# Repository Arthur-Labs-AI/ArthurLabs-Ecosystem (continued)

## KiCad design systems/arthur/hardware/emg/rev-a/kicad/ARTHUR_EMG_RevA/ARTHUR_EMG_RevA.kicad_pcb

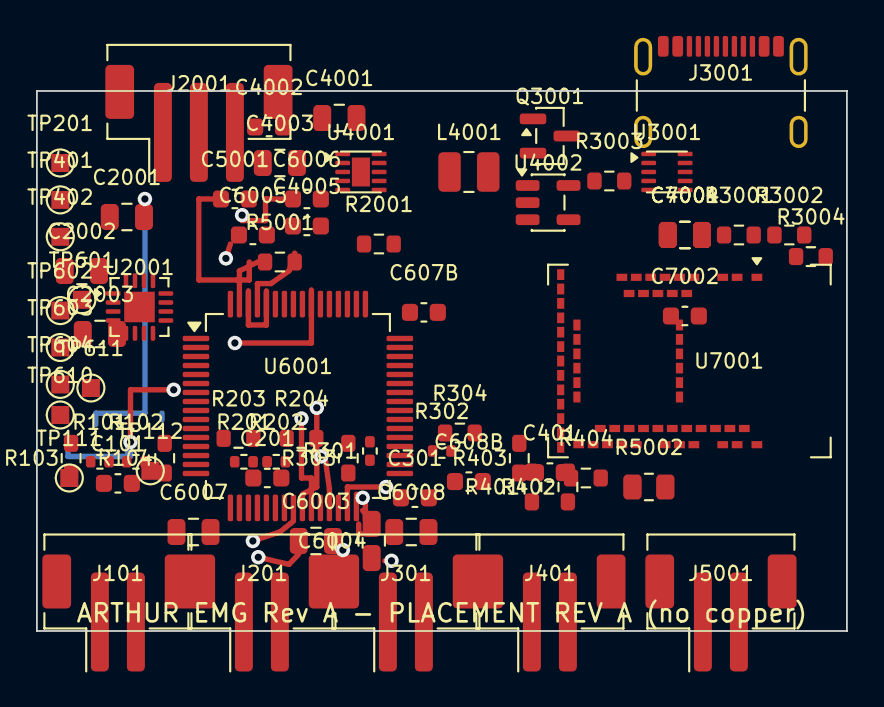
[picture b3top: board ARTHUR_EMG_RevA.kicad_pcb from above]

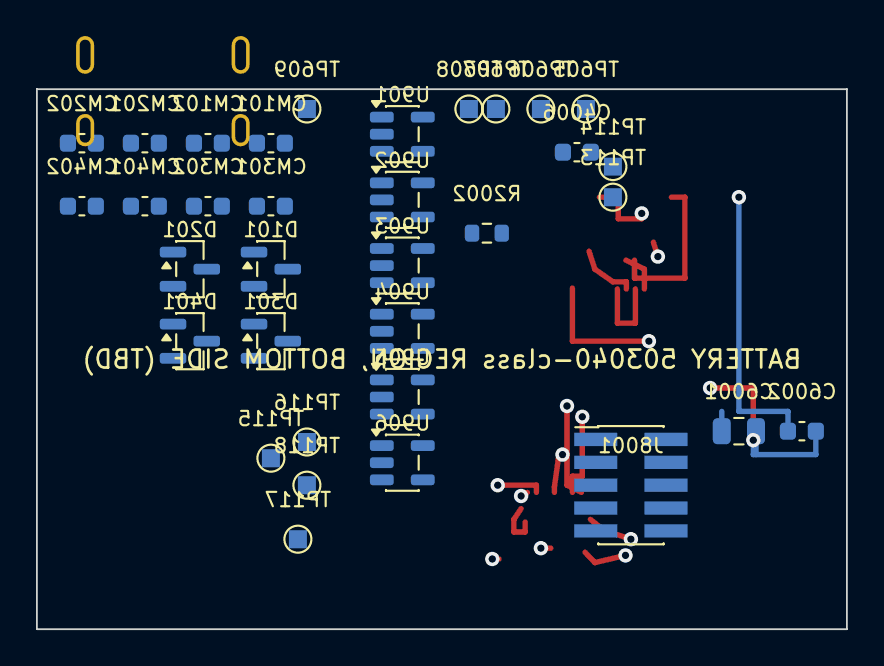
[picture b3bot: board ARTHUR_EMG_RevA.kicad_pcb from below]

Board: 4 copper layers, 45.0 x 30.0 mm, 106 parts (34 on the bottom side), 54 nets.

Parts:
C101, C201, C301, C401: 4.7nF C0G; C_0603_1608Metric
C607B, C608B, C4002, C6002, C7002: 0.1u; C_0603_1608Metric
C2001: 1u; C_0805_2012Metric
C2002, C2003, C7001: 4.7u; C_0805_2012Metric
C4001, C4003, C4004, C6001: 10u; C_0805_2012Metric
C4005, C4006, C6004, C6005, C6006, C6007, C6008: 1u; C_0603_1608Metric
C5001: 1.5nF; C_0603_1608Metric
C6003: 22u; C_0805_2012Metric
CM101, CM102, CM201, CM202, CM301, CM302, CM401, CM402: 470p DNP; C_0603_1608Metric
D101, D201, D301, D401: TVS DNP; SOT-23
J101: EMG-CH1; JST_PH_B2B-PH-SM4-TB_1x02-1MP_P2.00mm_Vertical
J201: EMG-CH2; JST_PH_B2B-PH-SM4-TB_1x02-1MP_P2.00mm_Vertical
J301: EMG-CH3; JST_PH_B2B-PH-SM4-TB_1x02-1MP_P2.00mm_Vertical
J401: EMG-CH4; JST_PH_B2B-PH-SM4-TB_1x02-1MP_P2.00mm_Vertical
J2001: LiPo-3P; JST_PH_B3B-PH-SM4-TB_1x03-1MP_P2.00mm_Vertical
J3001: USB-C-16P; USB_C_Receptacle_GCT_USB4105-xx-A_16P_TopMnt_Horizontal
J5001: RLD; JST_PH_B2B-PH-SM4-TB_1x02-1MP_P2.00mm_Vertical
J8001: SWD-10; PinHeader_2x05_P1.27mm_Vertical_SMD
L4001: 1.5uH; L_1008_2520Metric
Q3001: 2N7002; SOT-23
R101, R102, R201, R202, R301, R302: 2.2k 1%; R_0402_1005Metric
R103, R104, R203, R204, R303, R304, R403, R404: 390k 1%; R_0603_1608Metric
R401, R402: 2.2k 1%; R_0603_1608Metric
R2001: 3.57k; R_0603_1608Metric
R2002: 3.24k; R_0603_1608Metric
R3001, R3002: 5.1k; R_0603_1608Metric
R3003, R3004: 100k; R_0603_1608Metric
R5001: 1M; R_0603_1608Metric
R5002: 100k; R_0805_2012Metric
TP111, TP112, TP113, TP114, TP115, TP116, TP117, TP118, TP201, TP401, TP402, TP601, TP602, TP603, TP604, TP605, TP606, TP607, TP608, TP609, TP610, TP611: TP_SMD; TP_SMD_1x1mm
U901, U902, U903, U904, U905, U906: SN74LVC1G125; SOT-23-5
U2001: BQ24074RGTR; QFN-16-1EP_3x3mm_P0.5mm_EP1.7x1.7mm
U3001: TPD4E05U06DQAR; TPD4E05U06_DQA_2x2mm_P0.5mm
U4001: TPS63031DSKR; TPS63031_DSK_2.5x2.0mm_P0.5mm
U4002: TPS7A2030PDBVR; SOT-23-5
U6001: ADS1294IPAG; TQFP-64_10x10mm_P0.5mm
U7001: MDBT50Q-1MV2; Raytac_MDBT50Q

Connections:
3V3: C608B.1, C4003.1, C4004.1, C4005.1, C6008.1, C7001.1, C7002.1, J8001.1, R3003.1, TP401.1, U4001.1, U4001.10, U4002.1, U6001.48, U6001.50, U6001.52, U7001.28, U7001.30
AFE_3V0: C607B.1, C4006.1, C6007.1, TP601.1, U901.5, U902.5, U903.5, U904.5, U905.5, U906.5, U4002.5, U6001.1, U6001.2, U6001.3, U6001.4, U6001.5, U6001.6, U6001.7, U6001.8, U6001.19, U6001.21, U6001.22, U6001.54, U6001.56, U6001.59
AFE_CS_N: TP607.1, U903.4, U6001.39
AFE_DRDY_N: TP608.1, U6001.47, U7001.41
AFE_ENABLE: Q3001.3, R3003.2, U4002.3
AFE_MISO: TP606.1, U6001.43, U7001.39
AFE_MOSI: TP605.1, U902.4, U6001.34
AFE_PWDN_N: TP611.1, U906.4, U6001.35
AFE_RESET_N: TP610.1, U905.4, U6001.36
AFE_SCLK: TP604.1, U901.4, U6001.40
AFE_START: TP609.1, U904.4, U6001.38
BAT+: C2003.1, J2001.1, TP201.1, U2001.2, U2001.3
CC1: J3001.A5, R3001.1, U3001.4
CC2: J3001.B5, R3002.1, U3001.5
CH1_N: C101.2, CM102.1, D101.3, R102.2, R104.1, TP112.1, U6001.15
CH1_P: C101.1, CM101.1, D101.1, R101.2, R103.1, TP111.1, U6001.16
CH2_N: C201.2, CM202.1, D201.3, R202.2, R204.1, TP114.1, U6001.13
CH2_P: C201.1, CM201.1, D201.1, R201.2, R203.1, TP113.1, U6001.14
CH3_N: C301.2, CM302.1, D301.3, R302.2, R304.1, TP116.1, U6001.11
CH3_P: C301.1, CM301.1, D301.1, R301.2, R303.1, TP115.1, U6001.12
CH4_N: C401.2, CM402.1, D401.3, R402.2, R404.1, TP118.1, U6001.9
CH4_P: C401.1, CM401.1, D401.1, R401.2, R403.1, TP117.1, U6001.10
CHG_N: U2001.9, U7001.45
ELECTRODE_N: J101.2, J201.2, J301.2, J401.2, R102.1, R202.1, R302.1, R402.1
ELECTRODE_P: J101.1, J201.1, J301.1, J401.1, R101.1, R201.1, R301.1, R401.1
GND: C607B.2, C608B.2, C2001.2, C2002.2, C2003.2, C4001.2, C4002.2, C4003.2, C4004.2, C4005.2, C4006.2, C6001.2, C6002.2, C6003.2, C6004.2, C6005.2, C6006.2, C6007.2, C6008.2, C7001.2, C7002.2, CM101.2, CM102.2, CM201.2, CM202.2, CM301.2, CM302.2, CM401.2, CM402.2, D101.2, D201.2, D301.2, D401.2, J101.MP, J201.MP, J301.MP, J401.MP, J2001.3, J2001.MP, J3001.A1, J3001.A12, J3001.B1, J3001.B12, J5001.2, J5001.MP, J8001.3, J8001.5, J8001.9, Q3001.2, R2001.2, R2002.2, R3001.2, R3002.2, R3004.2, TP402.1, U901.1, U901.3, U902.1, U902.3, U903.1, U903.3, U904.1, U904.3, U905.1, U905.3, U906.1, U906.3, U2001.4, U2001.5, U2001.8, U2001.17, U3001.3, U3001.8, U4001.3, U4001.7, U4001.9, U4001.11, U4002.2, U6001.20, U6001.23, U6001.25, U6001.31, U6001.32, U6001.33, U6001.41, U6001.49, U6001.51, U6001.53, U6001.57, U6001.58, U7001.1, U7001.2, U7001.15, U7001.33, U7001.55
ICHG_SET_TBD: R2001.1, U2001.16
ILIM_SET_TBD: R2002.1, U2001.12
MCU_CS_N: U903.2, U7001.38
MCU_MOSI: U902.2, U7001.36
MCU_PWDN_N: U906.2, U7001.43
MCU_RESET_N: J8001.10, U7001.40
MCU_RESET_N_AFE: U905.2, U7001.44
MCU_SCLK: U901.2, U7001.37
MCU_START: U904.2, U7001.42
PACK_NTC: J2001.2, U2001.1
PGOOD_N: U2001.7, U7001.48
RLDINV: C5001.2, R5001.2, U6001.61
RLDOUT: C5001.1, R5001.1, R5002.1, TP603.1, U6001.63
RLD_SAFE: J5001.1, R5002.2
SWDCLK: J8001.4, U7001.53
SWDIO: J8001.2, U7001.51
SW_L1: L4001.1, U4001.4
SW_L2: L4001.2, U4001.2
SYS_RAW: C2002.1, C4001.1, C4002.1, U2001.6, U2001.10, U2001.11, U4001.5, U4001.6, U4001.8
USB_D+: J3001.A6, J3001.B6, U3001.1, U7001.35
USB_D-: J3001.A7, J3001.B7, U3001.2, U7001.34
USB_VBUS: C2001.1, J3001.A4, J3001.A9, J3001.B4, J3001.B9, Q3001.1, R3004.1, U2001.13, U7001.32
VCAP1: C6003.1, U6001.28
VCAP2: C6004.1, U6001.30
VCAP3: C6005.1, U6001.55
VCAP4: C6006.1, U6001.26
VCM: R103.2, R104.2, R203.2, R204.2, R303.2, R304.2, R403.2, R404.2, TP602.1, U6001.60, U6001.62
VREFP_2V4: C6001.1, C6002.1, U6001.24

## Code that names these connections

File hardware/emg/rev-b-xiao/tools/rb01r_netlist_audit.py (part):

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# SCTF SX3M (3CM) family datasheet rev 05/12/2026, "Dimensions" page
DATASHEET_SCTF_3CM = {1: "OE", 2: "GND", 3: "OUT", 4: "VDD"}
# Seeed Studio XIAO ESP32S3 (wiki pinout + OPL_Kicad_Library symbol XIAO-ESP32-S3-SMD)
DATASHEET_XIAO = {1: "D0/GPIO1", 2: "D1/GPIO2", 3: "D2/GPIO3", 4: "D3/GPIO4", 5: "D4/GPIO5", 6: "D5/GPIO6",
                  7: "D6/GPIO43", 8: "D7/GPIO44", 9: "D8/GPIO7", 10: "D9/GPIO8", 11: "D10/GPIO9",
                  12: "3V3", 13: "GND", 14: "5V", 23: "BAT+"}

ADC_P = {1: 3, 2: 6, 3: 7, 4: 10}     # AINxP pin for EMG channel k (AIN0P=3, AIN1P=6, AIN2P=7, AIN3P=10)
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    return err


@check("P03", "VCM: U503A follower, B/C/D followers on VCM, U503 +IN behind 10k, no loop through patient pins")
def p03(n):
    err = []
    if not n.same(("U503", 1), ("U503", 2)):
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    return err


@check("S01", "Supplied RB-01R checks: patient pin 1 NC, MP pads NC, RLD 100k to VCM")
def s01(n):
    e = []
    if not n.nc("J5001", "1"):
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    return err


@check("B01", "X1: SCTF pins OE/VDD on DVDD_F, GND on GND, OUT behind the 33 ohm, 100 nF at the oscillator")
def b01(n):
    err = []
    if not n.same(("X1", 1), ("X1", 4), ("U6001", 20), ("C6010", 1)):
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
